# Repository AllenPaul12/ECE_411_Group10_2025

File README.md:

# ECE_411_Group10_2025
Repository for ECE 411 (Group 10) Fall 2025

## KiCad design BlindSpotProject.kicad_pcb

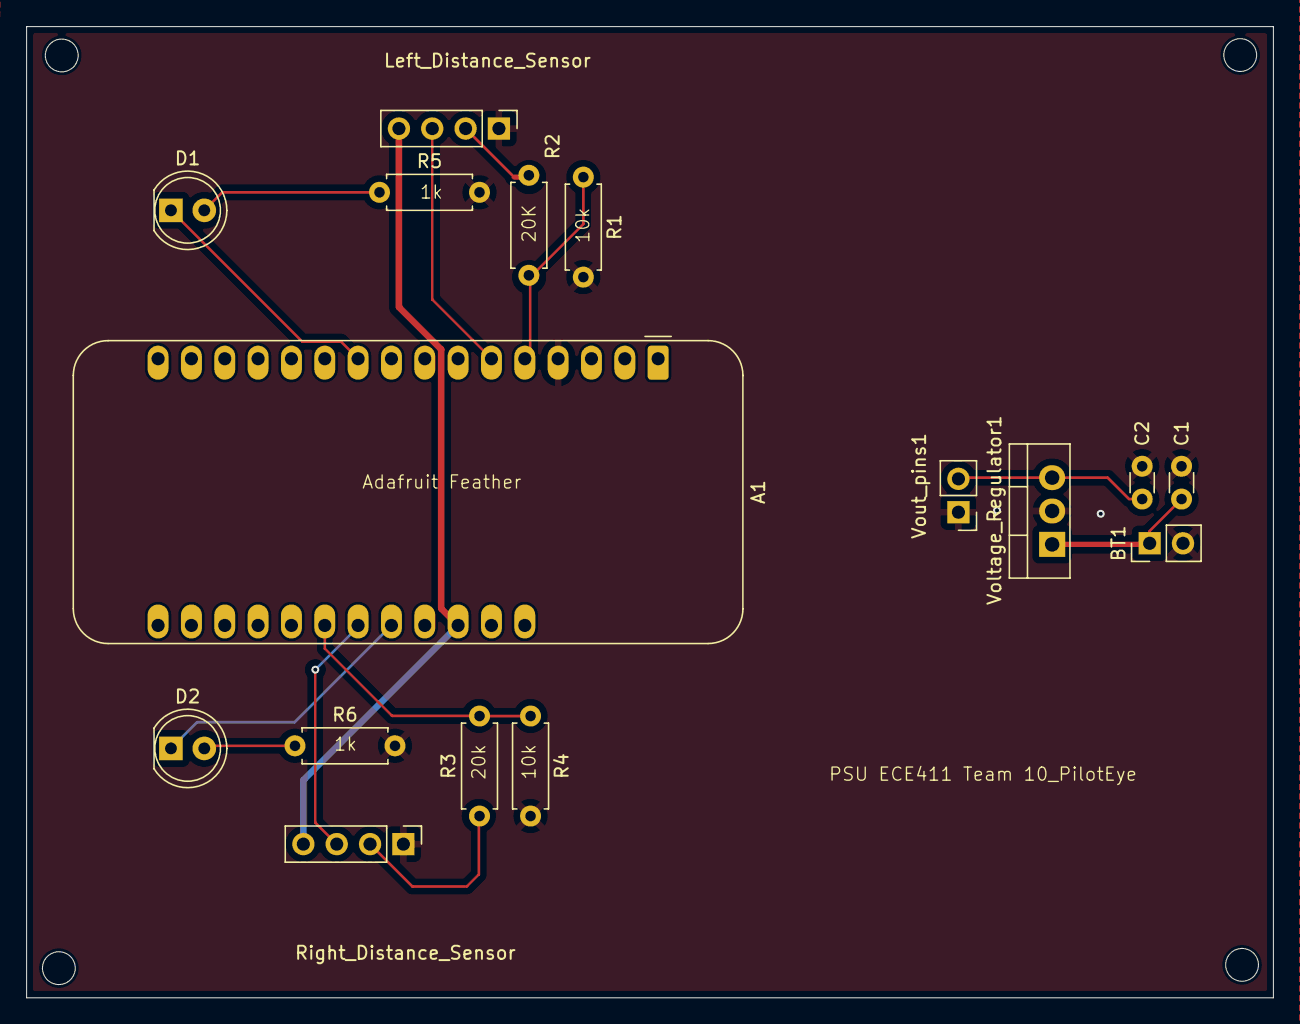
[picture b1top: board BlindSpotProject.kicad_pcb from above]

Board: 2 copper layers, 95.0 x 74.0 mm, 16 parts (0 on the bottom side), 13 nets.

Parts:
A1: Adafruit_Feather_HUZZAH32_ESP32; Adafruit_Feather
BT1: 9V; PinHeader_1x02_P2.54mm_Vertical
C1: 0.33u; C_Disc_D3.0mm_W1.6mm_P2.50mm
C2: 0.1u; C_Disc_D3.0mm_W1.6mm_P2.50mm
D1: LED_L; LED_D5.0mm
D2: LED_R; LED_D5.0mm
Left_Distance_Sensor: Conn_01x04_Pin; PinHeader_1x04_P2.54mm_Vertical
R1, R4: 20k; R_Axial_DIN0207_L6.3mm_D2.5mm_P7.62mm_Horizontal
R2, R3: 10k; R_Axial_DIN0207_L6.3mm_D2.5mm_P7.62mm_Horizontal
R5, R6: 1k; R_Axial_DIN0207_L6.3mm_D2.5mm_P7.62mm_Horizontal
Right_Distance_Sensor: Conn_01x04_Pin; PinHeader_1x04_P2.54mm_Vertical
Voltage_Regulator1: LM7805_TO220; TO-220-3_Vertical
Vout_pins1: Conn_01x02_Pin; PinHeader_1x02_P2.54mm_Vertical

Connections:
+5V: A1.26 (USB), C2.1, Left_Distance_Sensor.4, Right_Distance_Sensor.4, Voltage_Regulator1.3 (VO), Vout_pins1.2
/ECHO_L GPIO17: Left_Distance_Sensor.2, R2.1
GND: A1.4 (GND), BT1.2 (-), C1.2, C2.2, Left_Distance_Sensor.1, R1.2, R4.2, R5.2, R6.2, Right_Distance_Sensor.1, Voltage_Regulator1.2 (GND), Vout_pins1.1
unnamed: A1.22 (A9/IO33), R3.2, R4.1
unnamed: A1.23 (A10/IO27), Right_Distance_Sensor.3
unnamed: A1.24 (A11/IO12), D2.1 (K)
unnamed: A1.6 (DAC1/A1), Left_Distance_Sensor.3
unnamed: A1.5 (DAC2/A0), R1.1, R2.2
unnamed: A1.10 (IO4/A5), D1.1 (K)
unnamed: BT1.1 (+), C1.1, Voltage_Regulator1.1 (VI)
unnamed: D1.2 (A), R5.1
unnamed: D2.2 (A), R6.1
unnamed: R3.1, Right_Distance_Sensor.2

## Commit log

2025-10-28 Prelim. Schematic
    This is the preliminary schematic for the Pilot Eye.
2025-10-28 Design Matrix
2025-11-04 Practicum Planning
    Here is the collaborative site for practicum planning and scheduling.
2025-11-04 Practicum Planning
    Here is the link to the collaborative site:
    https://pdx955109.monday.com/boards/18347857550
2025-11-04 Rename Practicum Planning.pdf to Practicum Planning
2025-11-04 Practicum Planning
    The link to the collaborative site:
    https://pdx955109.monday.com/boards/18347857550
2025-11-06 Add files via upload
    all parts came in, we are now testing the sensors and seeing the breadboard layout as well as making sure everything is logically sound.
2025-11-11 L0 Pilot Eye
    This is the finished L0 Functional Decomp. of our produt Pilot Eye.
2025-11-11 L1 for Pilot Eye
    This is the L1 Functional Decomp. for our product Pilot Eye with the labeled interconnections.
2025-11-11 Bill of Materials
    Here is the full BOM (bill of materials) for the Pilot Eye.
2025-11-20 Final Cad Design
    PDFs of both the schematic and the PCB
2025-12-12 Add files via upload
    Final Schematic and PCB
